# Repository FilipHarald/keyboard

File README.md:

```sh
qmk list-keyboards
qmk config user.keyboard=atreus/astar_mirrored
qmk config user.keymap=filipharald
qmk new-keymap
nvim /home/filip/qmk_firmware/keyboards/atreus/keymaps/filipharald
```

```sh
qmk c2json -km filipharald -kb atreus /home/filip/qmk_firmware/keyboards/atreus/keymaps/filipharald/keymap.c > ~/Documents/map.json
```

first put keyboard in bootloader mode! (`QK_BOOT`)
```sh
qmk compile
lsusb | grep Atreus
qmk flash
```

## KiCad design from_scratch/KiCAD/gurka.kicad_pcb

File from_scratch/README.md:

Trying to build it from scratch following this guide: https://flatfootfox.com/ergogen-introduction/

Except ordering PCB I've also bought...
- diodes THT - 100 pcs
- RP2040 MCUs - 2 pcs
- MCU-sockets - 2 pcs
- Kalih BOX Jade switches - 50 pcs
- TRRS sockets - 2 pcs
- TRRS cable
- MA Blank PBT 1U keycaps for MX Switches

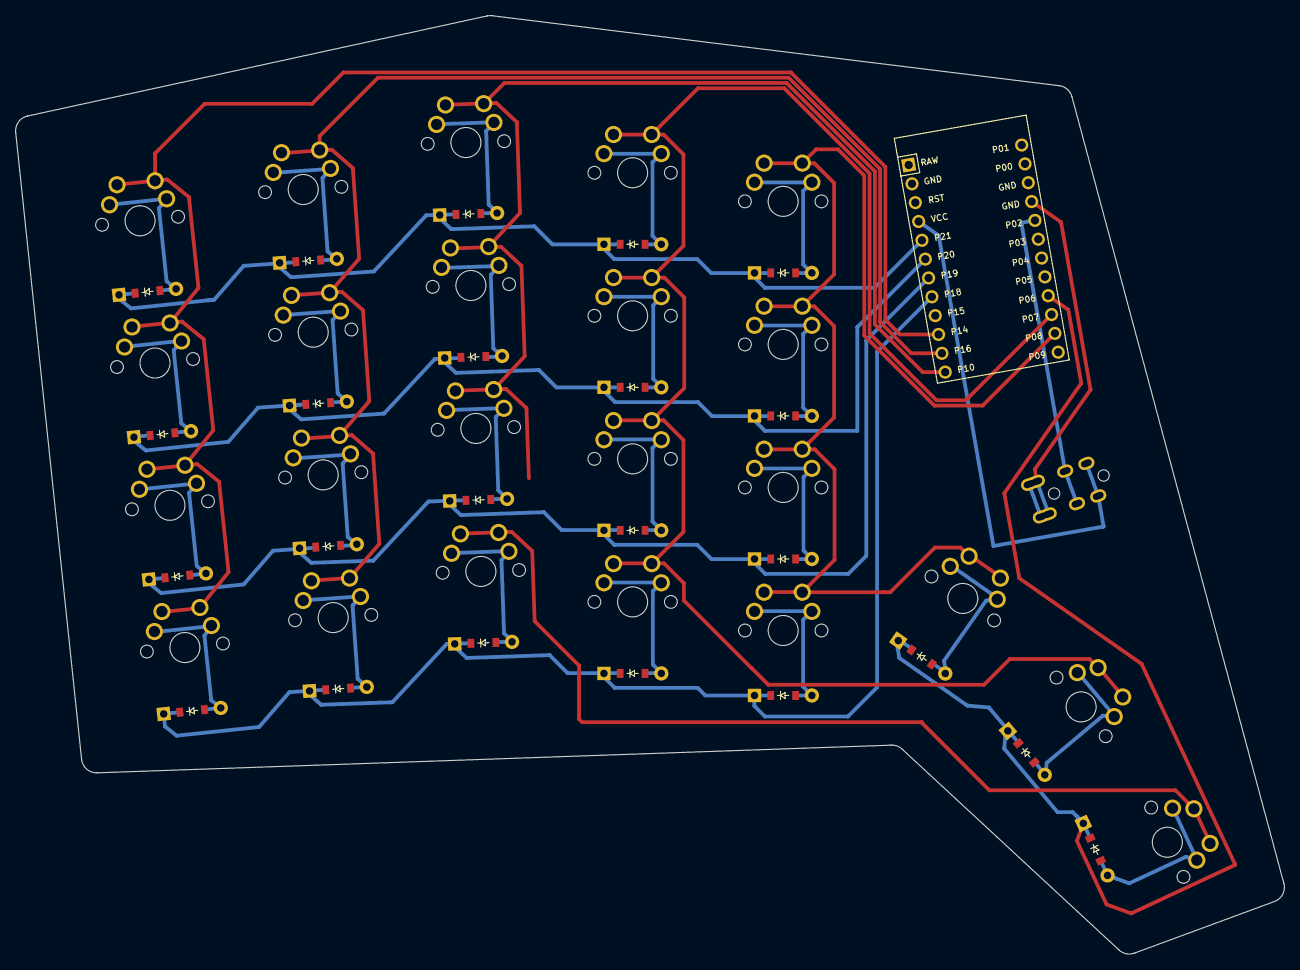
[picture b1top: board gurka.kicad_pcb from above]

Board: 2 copper layers, 168.5 x 124.6 mm, 48 parts (0 on the bottom side), 36 nets.

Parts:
D1, D2, D3, D4, D5, D6, D7, D8, D9, D10, D11, D12, D13, D14, D15, D16, D17, D18, D19, D20, D21, D22, D23: ComboDiode
MCU1: ProMicro
S1, S2, S3, S4, S5, S6, S7, S8, S9, S10, S11, S12, S13, S14, S15, S16, S17, S18, S19, S20, S21, S22, S23: MX
TRRS1: TRRS-PJ-320A-dual

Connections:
GND: MCU1.2, MCU1.15, MCU1.16, TRRS1.1, TRRS1.2
P2: MCU1.17, TRRS1.3
P6: D21.1, D22.1, D23.1, MCU1.21
P7: MCU1.22, S13.1, S14.1, S15.1, S16.1, S22.1
P8: MCU1.23, S17.1, S18.1, S19.1, S20.1, S21.1
P10: MCU1.12, S9.1, S10.1, S11.1, S12.1, S23.1
P14: MCU1.10, S1.1, S2.1, S3.1, S4.1
P16: MCU1.11, S5.1, S6.1, S7.1, S8.1
P18: D1.1, D5.1, D9.1, D13.1, D17.1, MCU1.8
P19: D2.1, D6.1, D10.1, D14.1, D18.1, MCU1.7
P20: D3.1, D7.1, D11.1, D15.1, D19.1, MCU1.6
P21: D4.1, D8.1, D12.1, D16.1, D20.1, MCU1.5
VCC: MCU1.4, TRRS1.4
fary_default: D23.2, S23.2
index_bottom: D14.2, S14.2
index_home: D15.2, S15.2
index_mod: D13.2, S13.2
index_top: D16.2, S16.2
inner_bottom: D18.2, S18.2
inner_home: D19.2, S19.2
inner_mod: D17.2, S17.2
inner_top: D20.2, S20.2
middle_bottom: D10.2, S10.2
middle_home: D11.2, S11.2
middle_mod: D9.2, S9.2
middle_top: D12.2, S12.2
pinky_bottom: D2.2, S2.2
pinky_home: D3.2, S3.2
pinky_mod: D1.2, S1.2
pinky_top: D4.2, S4.2
reachy_default: D22.2, S22.2
ring_bottom: D6.2, S6.2
ring_home: D7.2, S7.2
ring_mod: D5.2, S5.2
ring_top: D8.2, S8.2
tucky_default: D21.2, S21.2

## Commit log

2023-03-11 version 1
2023-03-11 version 2
2023-03-11 version 2.1
2023-03-11 version 2.2
2023-03-11 version 2.3
2023-10-23 moved atreus/astar to seperate directory
2023-12-02 trying to build keyboard from scratch
2023-12-02 added first version of PCB and some tweaks
2023-12-03 updated trrs pin
2023-12-29 some adjustments to layout keys and diodes
2024-01-01 changed TRRS serial pin
2024-01-01 added pcb with routing
2024-01-25 WIP: from_scratch qmk
2024-01-25 chore: removed unused readmes
2024-08-20 less tapping
2025-12-18 circuit-breaker
